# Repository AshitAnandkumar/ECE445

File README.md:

# ECE445

## **Date:** September 23, 2025  
Sensory Subsystem Initial Research  

### Work Completed
Reviewed the approved project proposal and clarified project requirements. The posture checker must be compact, wearable, low power, and capable of detecting changes in body posture over time

Investigated into potential sensing approaches:
- Inertial Measurement Units (IMUs)
- Flex/stretch sensors
- Pressure sensors
- Tilt switches

Tilt switches were ruled out due to binary output. Pressure sensors were considered unreliable because of inconsistent contact with the body. Flex sensors were considered but noted to be prone to drift and mechanical fatigue

### Notes
IMU-based sensing in combination with stretch sensors were considered as the most suitable approach for posture monitoring

---

## **Date:** September 30, 2025  
Sensor comparison and IMU Selection

### Work Completed
Compared sensor options based on accuracy, size, power consumption, compatibility and price. Then reviewed datasheets and designs for shortlisted IMUs. Selected the **ICM-20948** IMU as the most suitable option for this project

**Summary of findings on different sensor options:**
- **Flex sensors:** Low cost but inconsistent and subject to wear
- **Single-axis accelerometers:** Insufficient orientation information
- **6-axis IMUs:** Functional but limited options and compatibility
- **9-axis IMUs:** Best overall capability for posture detection

Reviewed commonly used IMUs including MPU-6050, MPU-9250, and ICM-20948

**Justification of choses IMU-20948:**
- Integrated accelerometer, gyroscope, and magnetometer
- Small form factor matches our project goals
- Low-power operating modes to help ensure battery life is maintained
- I²C communication compatible with the MCU 
- Lots of available libraries to help program the IMU

### Notes
9-axis IMUs selected as preferred sensor class due to its flexibility and future project progression. Withing the 0-acis IMU options the ICM-20948 was chosen as the primary posture sensor as it was the most suitable IMU

---

## **Date:** October 7, 2025  
IMU-20948 requirements and design choices

### Work Completed
How the Sensor subsystem interacts with other subsystems:
- **Microcontroller:** I²C communication for data processing
- **Power subsystem:** 3.3V and 1.8V supplied to the IMU
- **Feedback subsystem:** Connected through the MCU to provide a feedback to the user

### Notes / Decisions
Confirmed how the Sensor subsystem works with other subsystems to see how to design it

---

## **Date:** October 14, 2025  
Schematics layout design  

### Work Completed
Reviewed ICM-20948 reference schematics. Identified required other components required:
- Decoupling capacitors near power pins
- Pull-up resistors on I²C lines
- Voltage regulator for 3.3V and 1.8V supply (Came from power subsystem)
- Level shifting required to communicate with MCU

Discussed sensor placement to maintain a consistent coordinate frame relative to user posture

### Notes
Schematic Completed based on datasheet and requirements. 

*Datasheets and schematics are uploaded in the Git repository for reference*

---

## **Date:** October 28, 2025  
PCB Layout and Sensor Placement  

### Work Completed
Reviewed IMU PCB layout guidelines:
- Short I²C traces
- Close placement of decoupling capacitors
- Avoidance of noisy digital signals near sensor

Determined IMU orientation on PCB to align axes with posture directions

### Notes
IMU orientation selected and PCB design completed

*PCB designs are uploaded in the Git repository for reference*

---

## **Date:** November 4, 2025 
Testing and Verification Planning  

### Work Completed
Defined test procedures:
- Power-on verification
- I²C communication check
- Static orientation testing
- Dynamic movement testing

Planned to record raw sensor outputs and verify repeatability/accuracy across tests

### Notes / Decisions
Testing focused on stability and repeatability rather than full accuracy

---

## **Date:** November 11, 2025  
Sensory Subsystem initial Testing and Debugging

### Work Completed
Verified IMU communication with the MCU and confirmed correct device identification. Observed stable accelerometer readings under static conditions.

Simulated posture changes by rotating the device and observing sensor output response

### Issues Detected
Minor noise present in raw data, consistent with expected results and doesnt have a huge impact on the data

---

## **Date:** November 17, 2025  
Enclosure Design and Mechanical Integration  

### Work Completed
Started initial CAD modeling of the device enclosure. The enclosure was designed to hold the PCB securely while maintaining a compact and wearable form factor suitable for a clip-on posture checker

Key considerations included PCB dimensions, component height clearances, and mounting features to prevent board movement. Openings were added and aligned for the push button and charging port to allow the user to access these features effortlessly

### Notes
Enclosure dimensions and cutout placements finalized to match the PCB layout and ensure proper alignment of the button and charging port

---

## **Date:** December 2, 2025 
Final Verification and Documentation  

### Work Completed
Confirmed IMU operation during integrated system testing. Sensor data successfully used to detect posture changes and trigger system feedback

Reviewed design decisions and the testing results for final documentation

### Notes
Sensory subsystem meets functional requirements

*Test results are uploaded in the Git repository for reference*

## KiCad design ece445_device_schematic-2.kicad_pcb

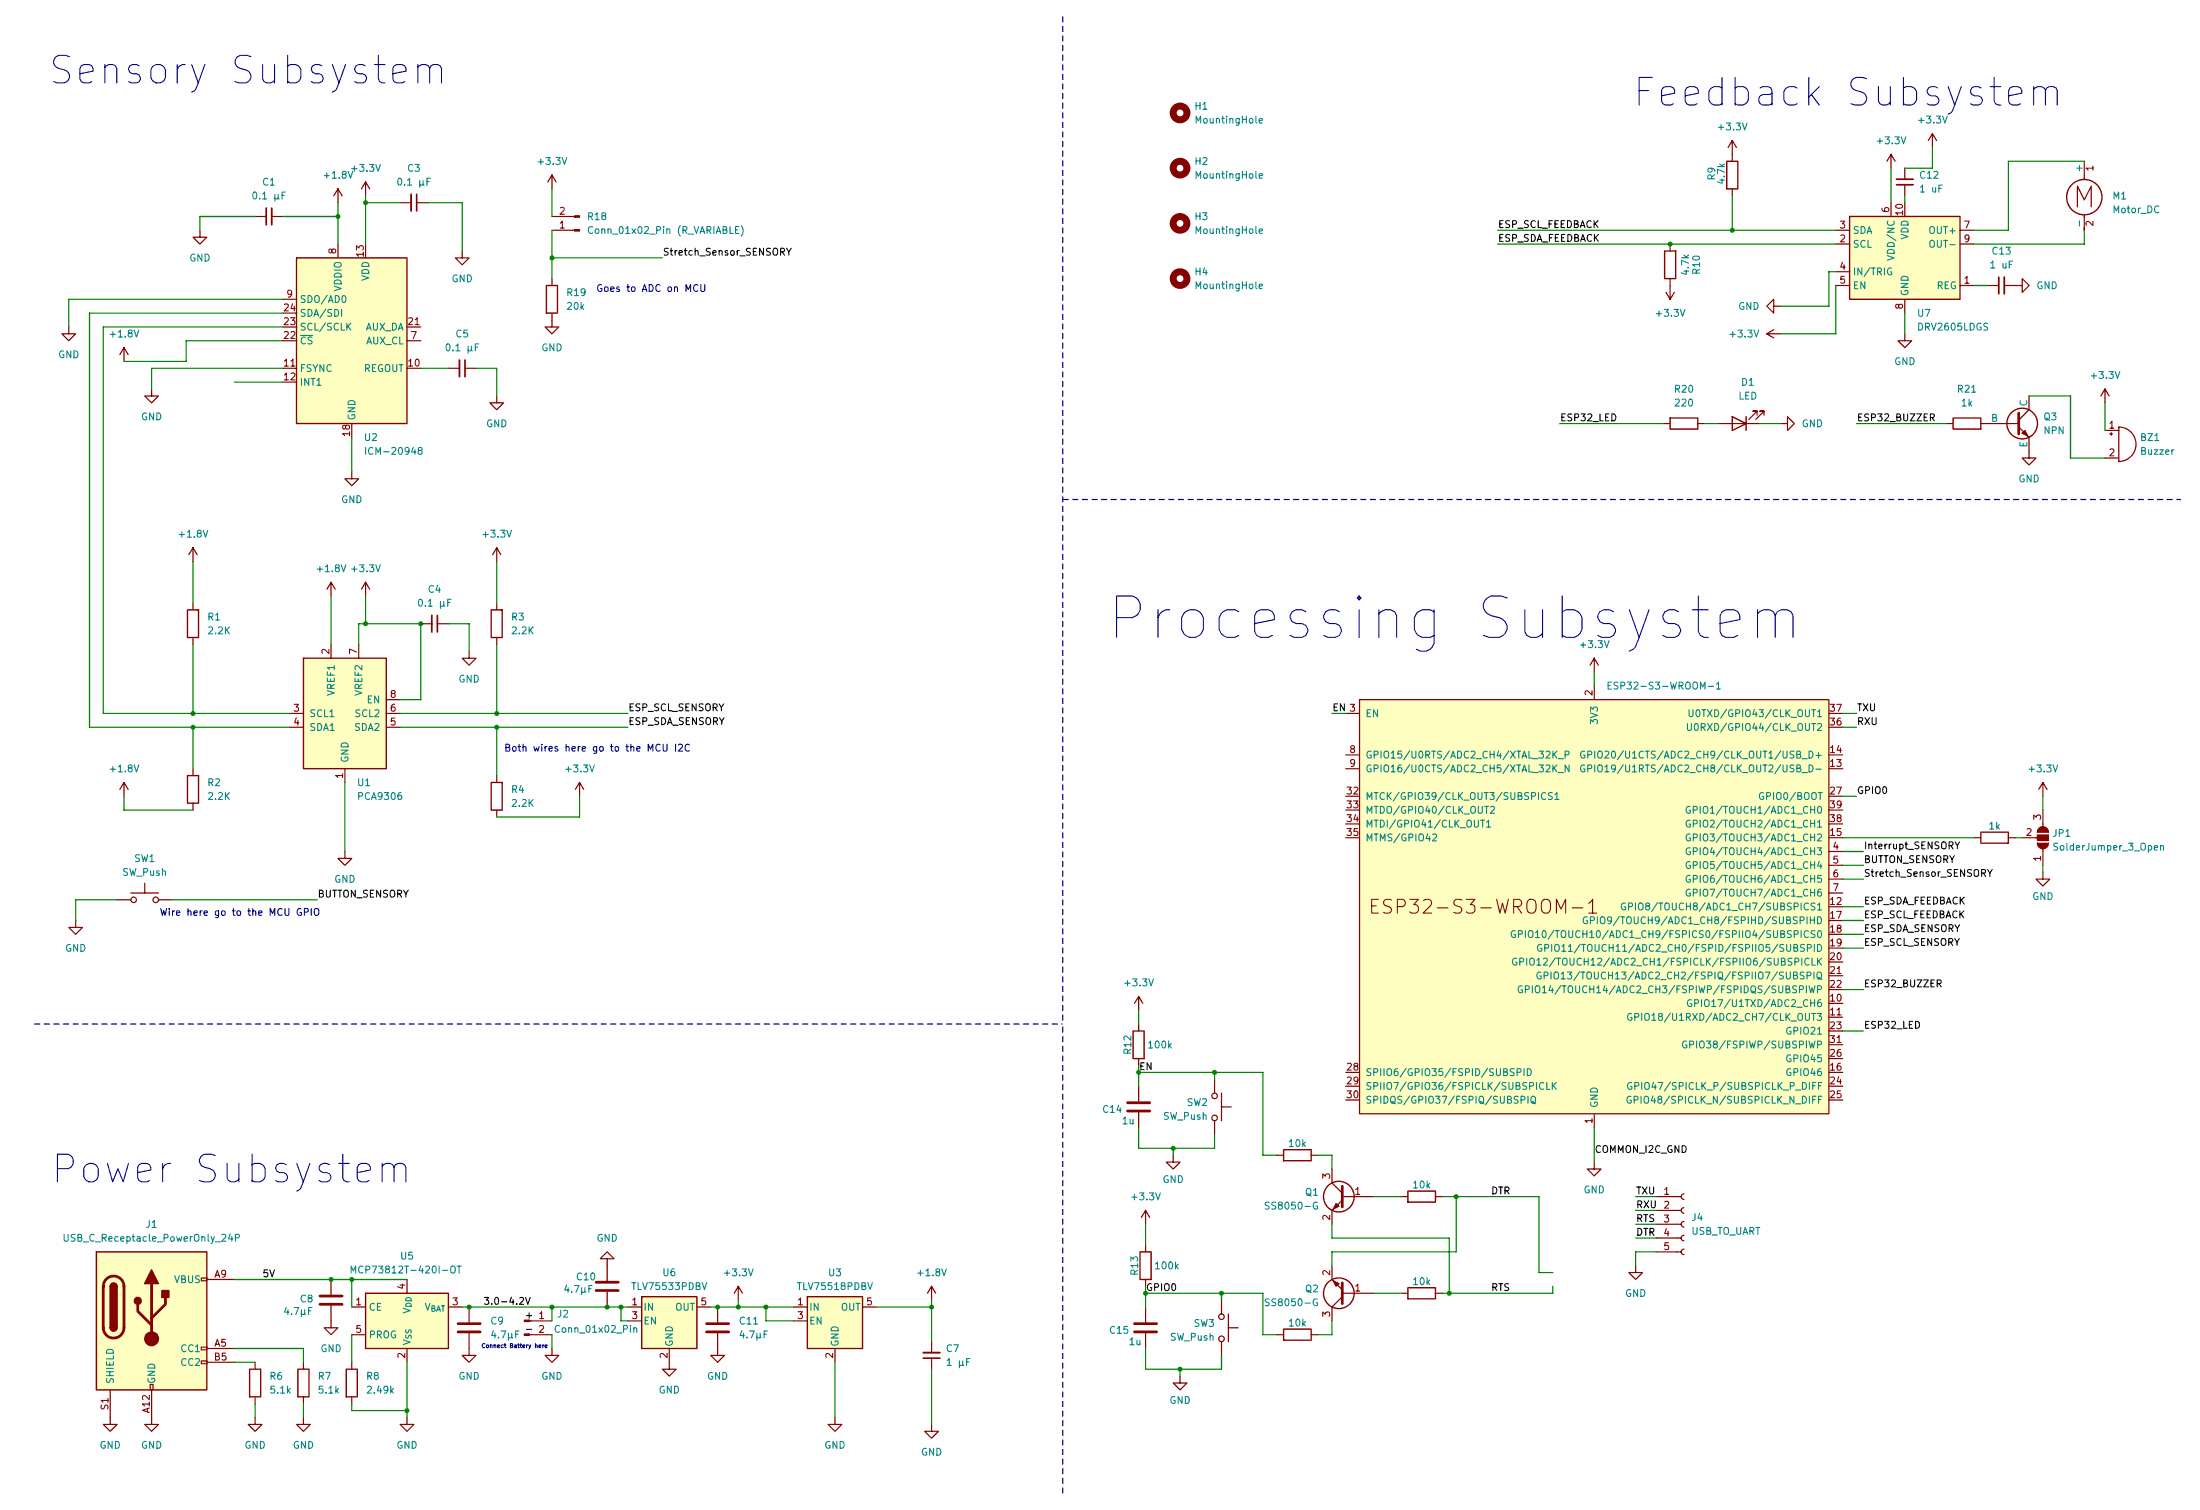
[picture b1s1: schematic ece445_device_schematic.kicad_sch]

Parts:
BZ1: Buzzer; Buzzer_12x9.5RM7.6
C1, C3, C4, C5: 0.1 μF; C_0805_2012Metric_Pad1.18x1.45mm_HandSolder
C7: 1 μF; C_0805_2012Metric_Pad1.18x1.45mm_HandSolder
C8, C9, C10, C11: 4.7µF; C_0805_2012Metric_Pad1.18x1.45mm_HandSolder
C12, C13: 1 uF; C_0805_2012Metric_Pad1.18x1.45mm_HandSolder
C14, C15: 1u; C_0805_2012Metric_Pad1.18x1.45mm_HandSolder
D1: LED; LED_0805_2012Metric_Pad1.15x1.40mm_HandSolder
H1, H2, H3, H4: MountingHole; MountingHole_3.2mm_M3
J1: USB_C_Receptacle_PowerOnly_24P; USB_C_Receptacle_GCT_USB4085
J2: Conn_01x02_Pin; PinHeader_1x02_P2.54mm_Vertical
J4: USB_TO_UART; PinHeader_1x05_P2.54mm_Vertical
JP1: SolderJumper_3_Open; SolderJumper-3_P2.0mm_Open_TrianglePad1.0x1.5mm
M1: Motor_DC; XDCR_C0720B001F
Q1, Q2: SS8050-G; SOT-23
Q3: NPN; SOT-23
R1, R2, R3, R4: 2.2K; R_0805_2012Metric_Pad1.20x1.40mm_HandSolder
R6, R7: 5.1k; R_0805_2012Metric_Pad1.20x1.40mm_HandSolder
R8: 2.49k; R_0805_2012Metric_Pad1.20x1.40mm_HandSolder
R9, R10: 4.7k; R_0805_2012Metric_Pad1.20x1.40mm_HandSolder
R11, R21: 1k; R_0805_2012Metric_Pad1.20x1.40mm_HandSolder
R12, R13: 100k; R_0805_2012Metric_Pad1.20x1.40mm_HandSolder
R14, R15, R16, R17: 10k; R_0805_2012Metric_Pad1.20x1.40mm_HandSolder
R18: Conn_01x02_Pin (R_VARIABLE); PinHeader_1x02_P2.54mm_Vertical
R19: 20k; R_0805_2012Metric_Pad1.20x1.40mm_HandSolder
R20: 220; R_0805_2012Metric_Pad1.20x1.40mm_HandSolder
SW1, SW2, SW3: SW_Push; SW_SPST_B3S-1000
U1: PCA9306; VSSOP-8_2.3x2mm_P0.5mm
U2: ICM-20948; InvenSense_QFN-24_3x3mm_P0.4mm
U3: TLV75518PDBV; SOT-23-5
U5: MCP73812T-420I-OT; SOT-23-5
U6: TLV75533PDBV; SOT-23-5
U7: DRV2605LDGS; VSSOP-10_3x3mm_P0.5mm
U8: ESP32-S3-WROOM-1; ESP32-S3-WROOM-1U

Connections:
+1.8V: C1.1, C7.2, R1.2, R2.1, U1.2 (VREF1), U2.8 (VDDIO), U2.22 (~CS), U3.5 (OUT)
+3.3V: BZ1.1 (+), C3.2, C4.2, C11.1, C12.2, JP1.3 (B), R3.2, R4.1, R9.1, R10.1, R12.1, R13.1, R18.2, U1.7 (VREF2), U1.8 (EN), U2.13 (VDD), U3.1 (IN), U3.3 (EN), U6.5 (OUT), U7.5 (EN), U7.6 (VDD/NC), U8.2 (3V3)
/3.0-4.2V: C9.1, C10.2, J2.1, U5.3 (V_{BAT}), U6.1 (IN), U6.3 (EN)
/5V: C8.1, J1.A4 (VBUS), J1.A9 (VBUS), J1.B4 (VBUS), J1.B9 (VBUS), U5.1 (CE), U5.4 (V_{DD})
/BUTTON_SENSORY: SW1.2, U8.5 (GPIO5/TOUCH5/ADC1_CH4)
/DTR: J4.4, Q2.2 (E), R16.1
/EN: C14.1, R12.2, R14.2, SW2.2, U8.3 (EN)
/ESP32_BUZZER: R21.1, U8.22 (GPIO14/TOUCH14/ADC2_CH3/FSPIWP/FSPIDQS/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)
/ESP32_LED: R20.2, U8.23 (GPIO21)
/ESP_SCL_FEEDBACK: R9.2, U7.3 (SDA), U8.17 (GPIO9/TOUCH9/ADC1_CH8/FSPIHD/SUBSPIHD)
/ESP_SCL_SENSORY: R3.1, U1.6 (SCL2), U8.19 (GPIO11/TOUCH11/ADC2_CH0/FSPID/FSPIIO5/S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)
/ESP_SDA_FEEDBACK: R10.2, U7.2 (SCL), U8.12 (GPIO8/TOUCH8/ADC1_CH7/SUBSPICS1)
/ESP_SDA_SENSORY: R4.2, U1.5 (SDA2), U8.18 (GPIO10/TOUCH10/ADC1_CH9/FSPICS0/FSPIIO4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)
/GPIO0: C15.1, R13.2, R15.2, SW3.2, U8.27 (GPIO0/BOOT)
/Interrupt_SENSORY: U8.4 (GPIO4/TOUCH4/ADC1_CH3)
/RTS: J4.3, Q1.2 (E), R17.1
/RXU: J4.2, U8.36 (U0RXD/GPIO44/CLK_OUT2)
/Stretch_Sensor_SENSORY: R18.1, R19.1, U8.6 (GPIO6/TOUCH6/ADC1_CH5)
/TXU: J4.1, U8.37 (U0TXD/GPIO43/CLK_OUT1)
GND: C1.2, C3.1, C4.1, C5.1, C7.1, C8.2, C9.2, C10.1, C11.2, C13.2, C14.2, C15.2, D1.1 (K), J1.A1 (GND), J1.A12 (GND), J1.B1 (GND), J1.B12 (GND), J1.S1 (SHIELD), J2.2, J4.5, JP1.1 (A), Q3.3 (E), R6.2, R7.2, R8.2, R19.2, SW1.1, SW2.1, SW3.1, U1.1 (GND), U2.9 (SDO/AD0), U2.11 (FSYNC), U2.18 (GND), U2.20 (GND), U3.2 (GND), U5.2 (V_{SS}), U6.2 (GND), U7.4 (IN/TRIG), U7.8 (GND), U8.1 (GND), U8.40 (GND), U8.41 (GND)
unnamed: BZ1.2 (-), Q3.1 (C)
unnamed: D1.2 (A), R20.1
unnamed: J1.A5 (CC1), R7.1
unnamed: J1.B5 (CC2), R6.1
unnamed: JP1.2 (C), R11.2
unnamed: M1.1 (+), U7.7 (OUT+)
unnamed: M1.2 (-), U7.9 (OUT-)
unnamed: Q1.1 (B), R16.2
unnamed: Q1.3 (C), R14.1
unnamed: Q2.1 (B), R17.2
unnamed: Q2.3 (C), R15.1
unnamed: Q3.2 (B), R21.2
unnamed: R1.1, U1.3 (SCL1), U2.23 (SCL/SCLK)
unnamed: R2.2, U1.4 (SDA1), U2.24 (SDA/SDI)
unnamed: C5.2, U2.10 (REGOUT)
unnamed: R8.1, U5.5 (PROG)
unnamed: C13.1, U7.1 (REG)
unnamed: C12.1, U7.10 (VDD)
unnamed: R11.1, U8.15 (GPIO3/TOUCH3/ADC1_CH2)

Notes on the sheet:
Sensory Subsystem
Goes to ADC on MCU
Processing Subsystem
Power Subsystem
Connect Battery here
Feedback Subsystem
Wire here go to the MCU GPIO
Both wires here go to the MCU I2C

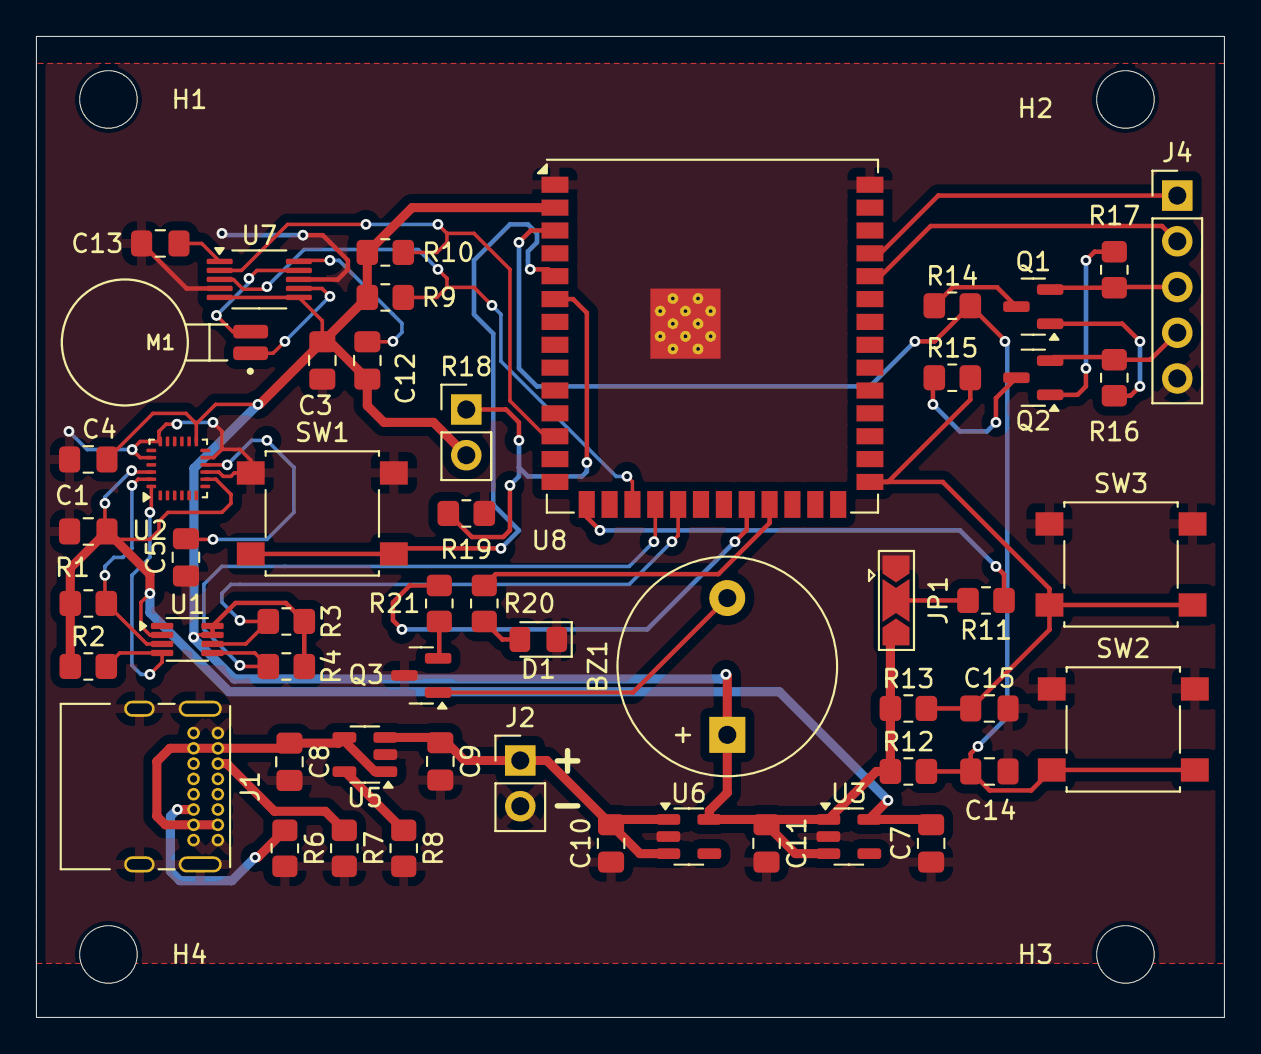
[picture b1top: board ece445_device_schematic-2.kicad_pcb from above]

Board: 2 copper layers, 66.0 x 54.5 mm, 57 parts (0 on the bottom side), 38 nets.

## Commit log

2025-12-18 Lab Notebook
